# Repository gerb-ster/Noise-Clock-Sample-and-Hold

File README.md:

# Noise, Clock and S&H

This module is a sort of 3-in-1 module, containing 4 types of noise, a clock generator based on a 555 IC and a sample-and-hold section. It’s based on / inspired by the Noise & S&H module by Niklas Ronnberg. It has a slew function, which is really nice, use it quit a lot.

The noise colors are White, Blue, Pink & Red. They are created by filtering the white noise. There are 2 trimmer pots on the back, one to set the overal noise volume and one to set the pulse length of the clock output.

## Status: Finished

- done: first schematic & board design
- done: breadboard and test
- done: design frontpanel
- done: order PCB and build prototype

## Pot Values

Since the earlier schematic didn't include the pot values, here they are (schematics have also been updated)

Slew & Attn: 100k lin
Rate: 1M log

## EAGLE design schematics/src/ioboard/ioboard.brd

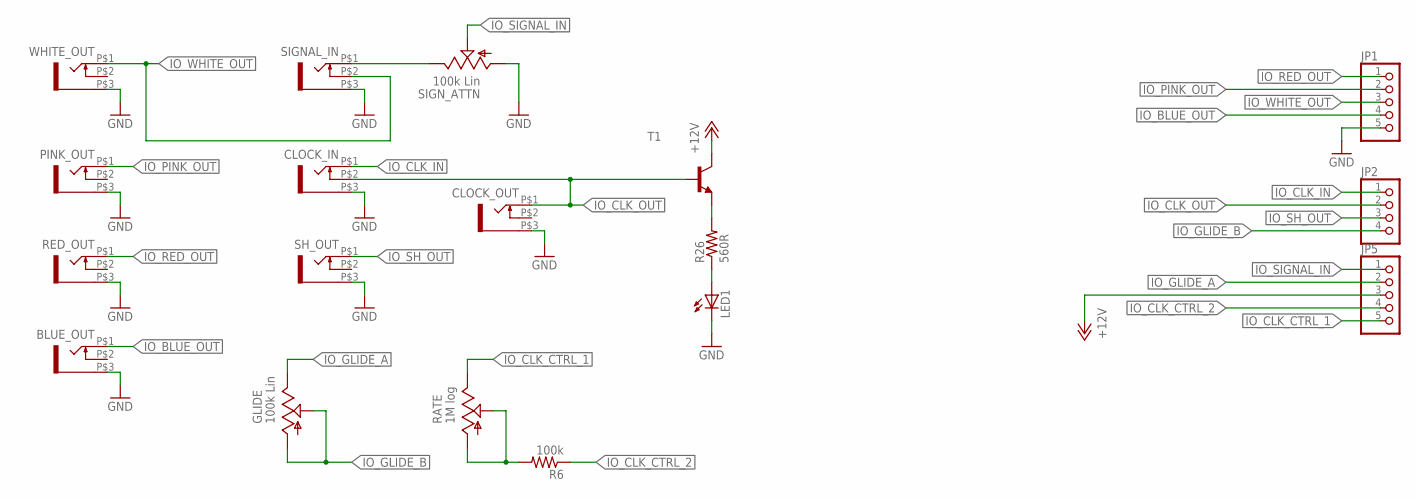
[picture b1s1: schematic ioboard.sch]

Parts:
BLUE_OUT: WQP-PJ301M-12_JACK
CLOCK_IN: WQP-PJ301M-12_JACK
CLOCK_OUT: WQP-PJ301M-12_JACK
GLIDE: 100k Lin; EVUF
JP1, JP5: PINHD-1X5; 1X05
JP2: PINHD-1X4; 1X04
LED1: LED3MM
PINK_OUT: WQP-PJ301M-12_JACK
R6: 100k; 0204/7
R26: 560R; 0204/7
RATE: 1M log; EVUF
RED_OUT: WQP-PJ301M-12_JACK
SH_OUT: WQP-PJ301M-12_JACK
SIGNAL_IN: WQP-PJ301M-12_JACK
SIGN_ATTN: 100k Lin; EVUF
T1: BC550-NPN-TO92-CBE; TO92-CBE
WHITE_OUT: WQP-PJ301M-12_JACK

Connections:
+12V: JP5.3, T1.C
GND: BLUE_OUT.P$3 (1), CLOCK_IN.P$3 (1), CLOCK_OUT.P$3 (1), JP1.5, LED1.K (C), PINK_OUT.P$3 (1), RED_OUT.P$3 (1), SH_OUT.P$3 (1), SIGNAL_IN.P$3 (1), SIGN_ATTN.1 (A), WHITE_OUT.P$3 (1)
IO_BLUE_OUT: BLUE_OUT.P$1 (2), JP1.4
IO_CLK_CTRL_1: JP5.5, RATE.3 (E)
IO_CLK_CTRL_2: JP5.4, R6.1
IO_CLK_IN: CLOCK_IN.P$1 (2), JP2.1
IO_CLK_OUT: CLOCK_IN.P$2 (3), CLOCK_OUT.P$1 (2), JP2.2, T1.B
IO_GLIDE_A: GLIDE.3 (E), JP5.2
IO_GLIDE_B: GLIDE.1 (A), GLIDE.2 (S), JP2.4
IO_PINK_OUT: JP1.2, PINK_OUT.P$1 (2)
IO_RED_OUT: JP1.1, RED_OUT.P$1 (2)
IO_SH_OUT: JP2.3, SH_OUT.P$1 (2)
IO_SIGNAL_IN: JP5.1, SIGN_ATTN.2 (S)
IO_WHITE_OUT: JP1.3, SIGNAL_IN.P$2 (3), WHITE_OUT.P$1 (2)
unnamed: SIGNAL_IN.P$1 (2), SIGN_ATTN.3 (E)
unnamed: LED1.A, R26.1
unnamed: R26.2, T1.E
unnamed: R6.2, RATE.1 (A), RATE.2 (S)

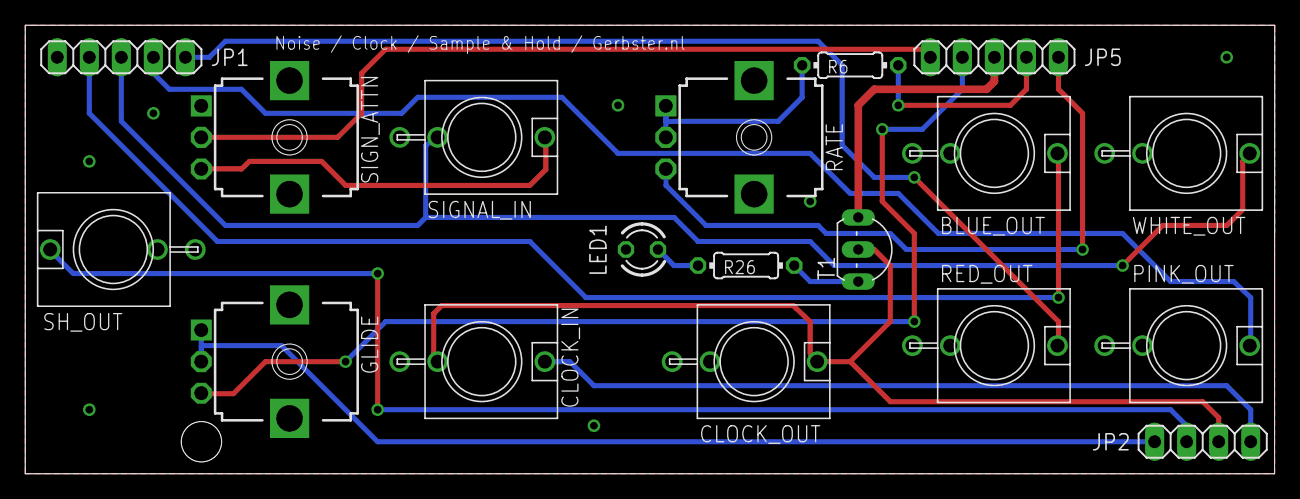
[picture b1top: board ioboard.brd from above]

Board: 2 copper layers, 99.1 x 35.6 mm, 18 parts (0 on the bottom side), 18 nets.

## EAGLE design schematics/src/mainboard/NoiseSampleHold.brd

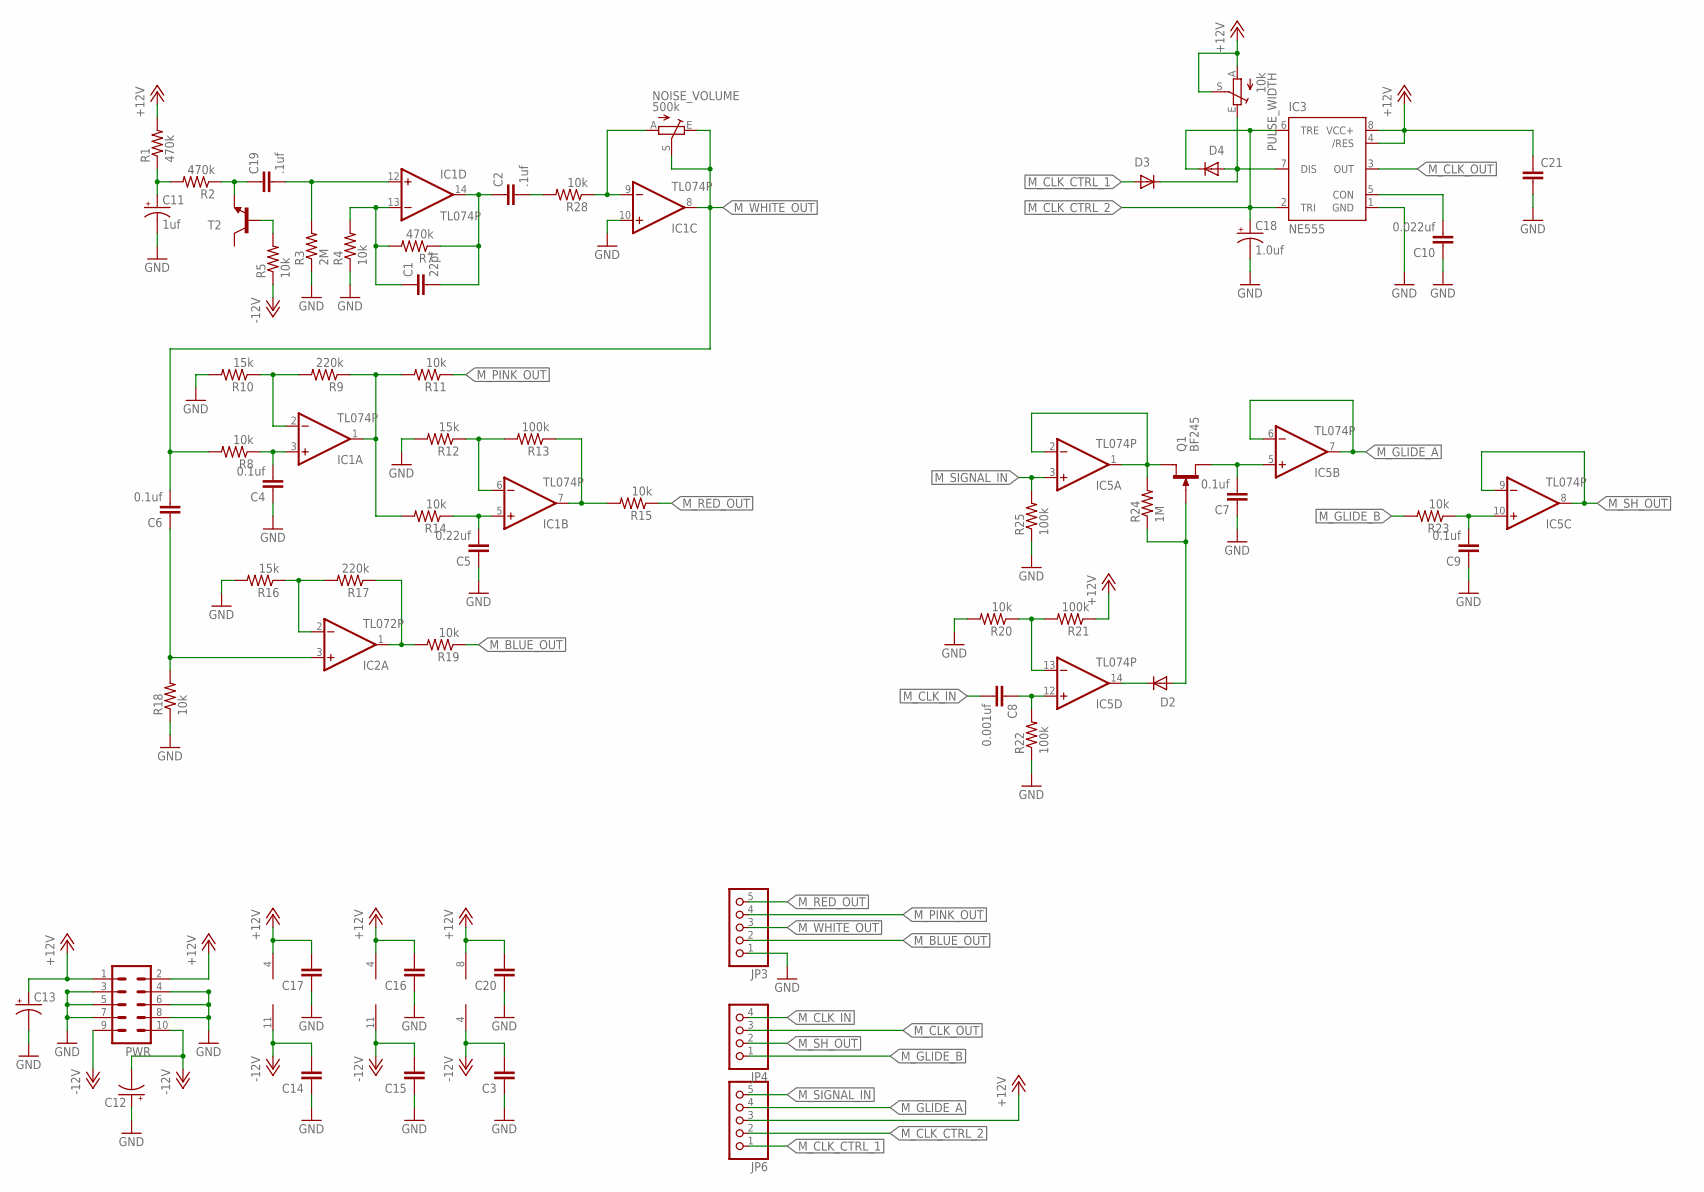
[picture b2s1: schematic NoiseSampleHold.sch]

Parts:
C1: 22pf; C050-024X044
C2, C19: .1uf; C050-024X044
C3, C14, C15, C16, C17, C20, C21: C-EU050-024X044; C050-024X044
C4, C6, C7, C9: 0.1uf; C050-024X044
C5: 0.22uf; C050-024X044
C8: 0.001uf; C050-024X044
C10: 0.022uf; C050-024X044
C11: 1uf; E2,5-5
C12, C13: CPOL-USE2.5-5; E2,5-5
C18: 1.0uf; E2,5-5
D2, D3, D4: 1N4148DO35-7; DO35-7
IC1, IC5: TL074P; DIL14
IC2: TL072P; DIL08
IC3: NE555; DIL-08
JP3, JP6: PINHD-1X5; 1X05
JP4: PINHD-1X4; 1X04
NOISE_VOLUME: 500k; S64YW
PULSE_WIDTH: 10k; S64YW
PWR: ML10
Q1: BF245; SOT54C
R1, R2, R7: 470k; 0204/7
R3: 2M; 0204/7
R4, R5, R8, R11, R14, R15, R18, R19, R20, R23, R28: 10k; 0204/7
R9, R17: 220k; 0204/7
R10, R12, R16: 15k; 0204/7
R13, R21, R22, R25: 100k; 0204/7
R24: 1M; 0204/7
T2: 2N3904-NPN-TO92-EBC; TO92-EBC

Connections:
+12V: C13.+, C16.2, C17.2, C20.2, C21.1, IC1.4 (V+), IC2.8 (V+), IC3.4 (/RES), IC3.8 (VCC+), IC5.4 (V+), JP6.3, PULSE_WIDTH.A, PULSE_WIDTH.S, PWR.1, PWR.2, R1.2, R21.1
-12V: C3.2, C12.-, C14.2, C15.2, IC1.11 (V-), IC2.4 (V-), IC5.11 (V-), PWR.9, PWR.10, R5.1
GND: C3.1, C4.1, C5.1, C7.1, C9.1, C10.1, C11.-, C12.+, C13.-, C14.1, C15.1, C16.1, C17.1, C18.-, C20.1, C21.2, IC1.10 (+IN), IC3.1 (GND), JP3.1, PWR.3, PWR.4, PWR.5, PWR.6, PWR.7, PWR.8, R3.1, R4.1, R10.2, R12.2, R16.2, R18.1, R20.2, R22.1, R25.1
M_BLUE_OUT: JP3.2, R19.1
M_CLK_CTRL_1: D3.A, JP6.1
M_CLK_CTRL_2: C18.+, D4.C, IC3.2 (TRI), IC3.6 (TRE), JP6.2
M_CLK_IN: C8.2, JP4.4
M_CLK_OUT: IC3.3 (OUT), JP4.3
M_GLIDE_A: IC5.6 (-IN), IC5.7 (OUT), JP6.4
M_GLIDE_B: JP4.1, R23.2
M_PINK_OUT: JP3.4, R11.1
M_RED_OUT: JP3.5, R15.1
M_SH_OUT: IC5.8 (OUT), IC5.9 (-IN), JP4.2
M_SIGNAL_IN: IC5.3 (+IN), JP6.5, R25.2
M_WHITE_OUT: C6.2, IC1.8 (OUT), JP3.3, NOISE_VOLUME.E, NOISE_VOLUME.S, R8.2
unnamed: C19.1, R2.1, T2.E
unnamed: C11.+, R1.1, R2.2
unnamed: R5.2, T2.B
unnamed: C19.2, IC1.12 (+IN), R3.2
unnamed: C1.1, IC1.13 (-IN), R4.2, R7.2
unnamed: C1.2, C2.1, IC1.14 (OUT), R7.1
unnamed: C2.2, R28.2
unnamed: C4.2, IC1.3 (+IN), R8.1
unnamed: IC1.2 (-IN), R9.2, R10.1
unnamed: IC1.1 (OUT), R9.1, R11.2, R14.2
unnamed: IC5.1 (OUT), IC5.2 (-IN), Q1.D, R24.2
unnamed: IC1.6 (-IN), R12.1, R13.2
unnamed: IC1.7 (OUT), R13.1, R15.2
unnamed: C5.2, IC1.5 (+IN), R14.1
unnamed: D3.C, D4.A, IC3.7 (DIS), PULSE_WIDTH.E
unnamed: C6.1, IC2.3 (+IN), R18.2
unnamed: IC2.2 (-IN), R16.1, R17.2
unnamed: IC2.1 (OUT), R17.1, R19.2
unnamed: C10.2, IC3.5 (CON)
unnamed: IC5.13 (-IN), R20.1, R21.2
unnamed: C8.1, IC5.12 (+IN), R22.2
unnamed: IC1.9 (-IN), NOISE_VOLUME.A, R28.1
unnamed: D2.C, IC5.14 (OUT)
unnamed: D2.A, Q1.G, R24.1
unnamed: C7.2, IC5.5 (+IN), Q1.S
unnamed: C9.2, IC5.10 (+IN), R23.1

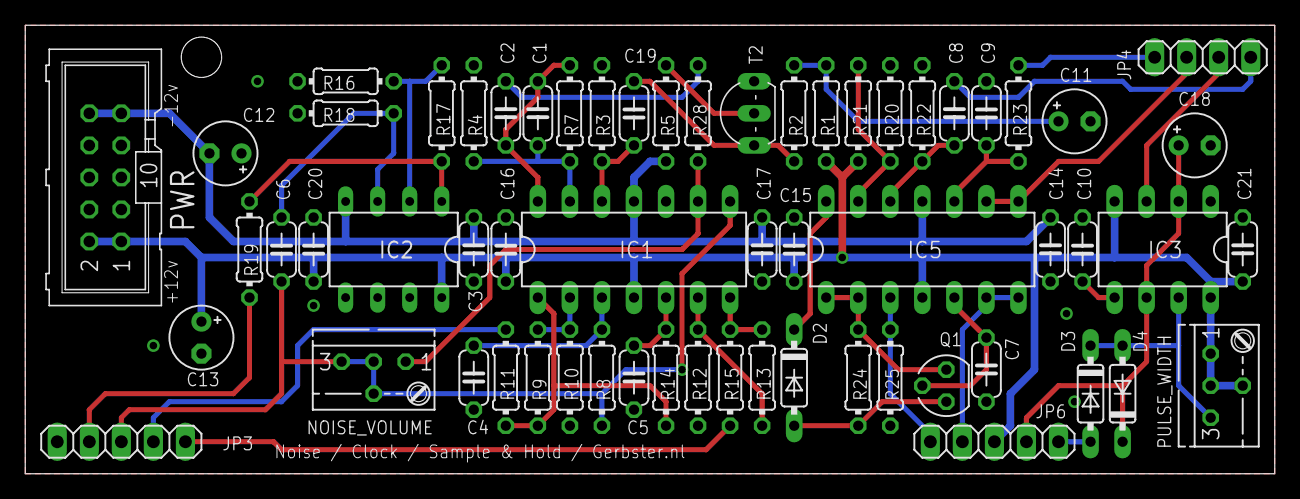
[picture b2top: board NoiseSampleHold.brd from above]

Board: 2 copper layers, 99.1 x 35.6 mm, 61 parts (0 on the bottom side), 41 nets.

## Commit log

2021-05-06 some files
2021-05-07 Added files & structure
2021-05-10 Added Status
2021-05-11 Added Status & Images
2021-08-06 Updated some schematics and docs
2021-08-10 Fixed some bugs and updated documentation
2022-04-20 Some updates & bugfixes
2022-04-22 Fixed schematics & descriptions
2022-05-17 Updated Firmware
2022-05-18 Updated Faceplates
2022-05-18 Fixed issues
2022-05-21 Fixed schematics
2022-05-28 General updates
